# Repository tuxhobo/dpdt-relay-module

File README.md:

# dpdt-relay-module
Simple relay module uses inexpensive 12V DC relays to control a 16VAC load.

Schematic and layout using KiCad 7.0

The PCB can ordered at https://www.jlcpcb.com reorder number Y1-6089045A.

Schematic:

Assembly:

Bill of Materials:
Ref | Digikey 			# | Description
-- | -- | --
D2 | 1N4148A0GCT-ND | 1N4148 			A0G  DIODE GEN PURP 100V 150MA DO35
K1 | 255-1733-ND | JW2ASN-DC12V 			 RELAY GEN PURPOSE DPST 5A 12V
C1 | 4191-EY1H221MP51012ECT-ND | EY1H221MP51012E 			 ALUMINUM ELECTROLYTIC CAPACITORS
J1 | 102-6149-ND | TB002-500-06BE 			 TERMINAL BLOCK, SCREW TYPE, 5.00
R1 | 13-CFR-50JB-52-270R-ND | CFR-50JB-52-270R 			 RES 270 OHM 5% 1/2W AXIAL
D1 | 641-1344-5-ND | DF005S-G 			 BRIDGE RECT 1PHASE 50V 1A DFS

For a complete description of how I used relay module for a video doorbell installation, see the following page:\
https://community.home-assistant.io/t/doorbell-automation-project/611389

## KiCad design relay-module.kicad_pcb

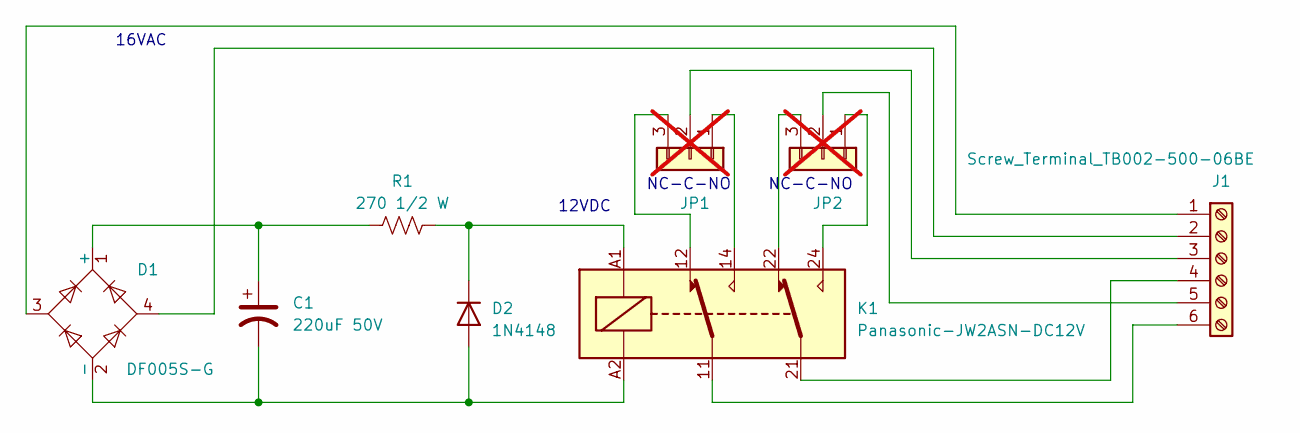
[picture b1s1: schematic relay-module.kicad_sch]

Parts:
C1: 220uF 50V; CP_Radial_D5.0mm_P2.50mm
D1: DF005S-G; Diode_Bridge_Vishay_DFS
D2: 1N4148; D_DO-35_SOD27_P7.62mm_Horizontal
J1: Screw_Terminal_TB002-500-06BE; TerminalBlock_RND_205-00049_1x06_P5.00mm_Horizontal
JP1, JP2: Conn_01x03; PinHeader_1x03_P2.54mm_Vertical; not fitted
K1: Panasonic-JW2ASN-DC12V; Relay_DPDT_Finder_40.52
R1: 270 1/2 W; R_Axial_DIN0414_L11.9mm_D4.5mm_P15.24mm_Horizontal

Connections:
unnamed: C1.1, D1.1 (+), R1.1
unnamed: C1.2, D1.2 (-), D2.2 (A), K1.A2
unnamed: D2.1 (K), K1.A1, R1.2
unnamed: D1.3, J1.1
unnamed: D1.4, J1.2
unnamed: J1.3, JP1.2
unnamed: J1.4, K1.21
unnamed: J1.5, JP2.2
unnamed: J1.6, K1.11
unnamed: JP1.1, K1.14
unnamed: JP1.3, K1.12
unnamed: JP2.1, K1.24
unnamed: JP2.3, K1.22

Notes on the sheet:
NC-C-NO
16VAC
12VDC

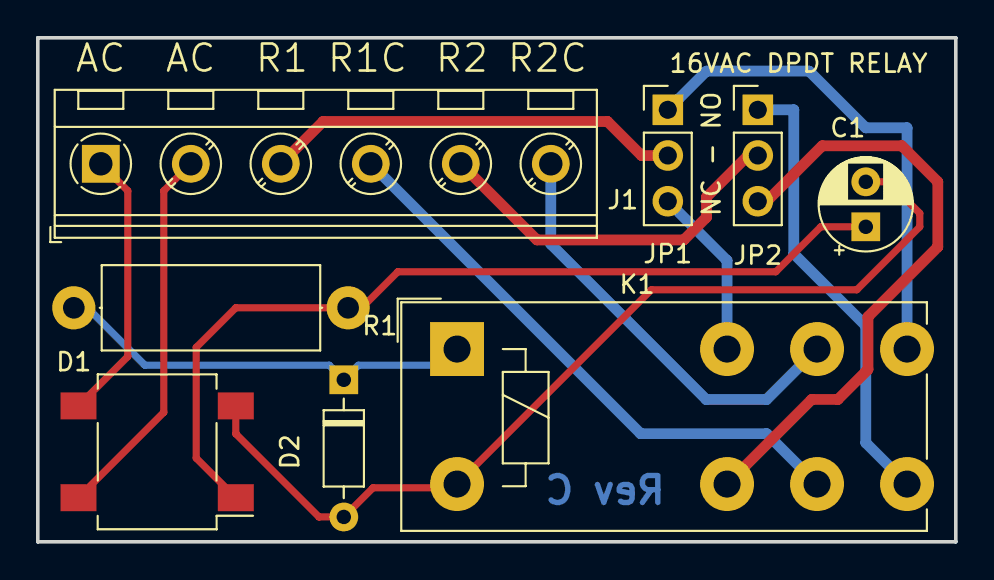
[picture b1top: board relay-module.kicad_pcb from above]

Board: 2 copper layers, 51.0 x 28.0 mm, 8 parts (0 on the bottom side), 13 nets.
